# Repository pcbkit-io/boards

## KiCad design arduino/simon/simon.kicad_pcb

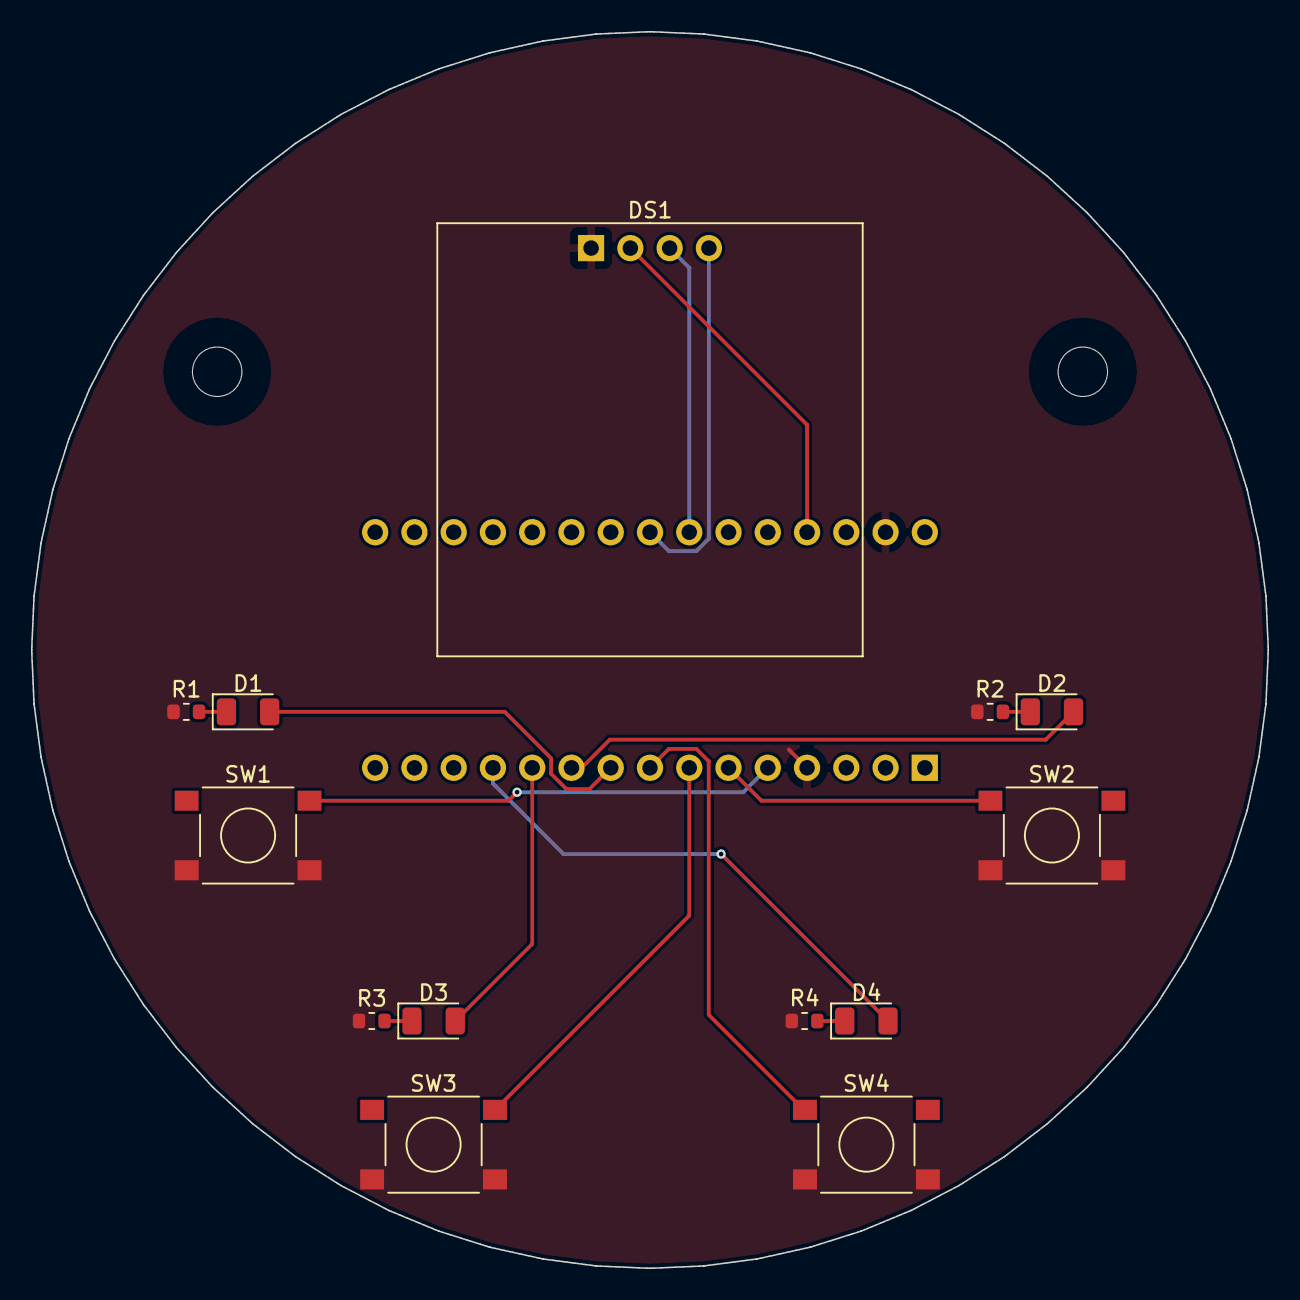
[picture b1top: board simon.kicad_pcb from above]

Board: 2 copper layers, 80.0 x 80.0 mm, 16 parts (1 on the bottom side), 16 nets.

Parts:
D1: green; LED_1206_3216Metric
D2: red; LED_1206_3216Metric
D3: blue; LED_1206_3216Metric
D4: yellow; LED_1206_3216Metric
DS1: SSD1306 0.96in 128x64 I2C OLED module; OLED_0.96in_I2C_Socket_1x04_P2.54mm
H1, H2: MountingHole_3.2mm_M3
NANO: A000005; Arduino_Nano_Socket_2x15_P2.54mm_W15.24mm
R1, R2, R3, R4: 680ohm; R_0603_1608Metric
SW1, SW2, SW3, SW4: PTS645SM43SMTR92 LFS; SW_Tactile_SPST_6x6mm_SMD

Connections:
B1: NANO.5 (D2), SW1.1 (a)
B2: NANO.6 (D3), SW2.1 (a)
B3: NANO.7 (D4), SW3.1 (a)
B4: NANO.8 (D5), SW4.1 (a)
GND: DS1.1 (GND), NANO.4 (GND), NANO.29 (GND), R1.2 (b), R2.2 (b), R3.2 (b), R4.2 (b), SW1.2 (b), SW2.2 (b), SW3.2 (b), SW4.2 (b)
K1: D1.1 (K), R1.1 (a)
K2: D2.1 (K), R2.1 (a)
K3: D3.1 (K), R3.1 (a)
K4: D4.1 (K), R4.1 (a)
L1: D1.2 (A), NANO.9 (D6)
L2: D2.2 (A), NANO.10 (D7)
L3: D3.2 (A), NANO.11 (D8)
L4: D4.2 (A), NANO.12 (D9)
SCL: DS1.3 (SCL), NANO.24 (A5)
SDA: DS1.4 (SDA), NANO.23 (A4)
V5: DS1.2 (VCC), NANO.27 (P5V)

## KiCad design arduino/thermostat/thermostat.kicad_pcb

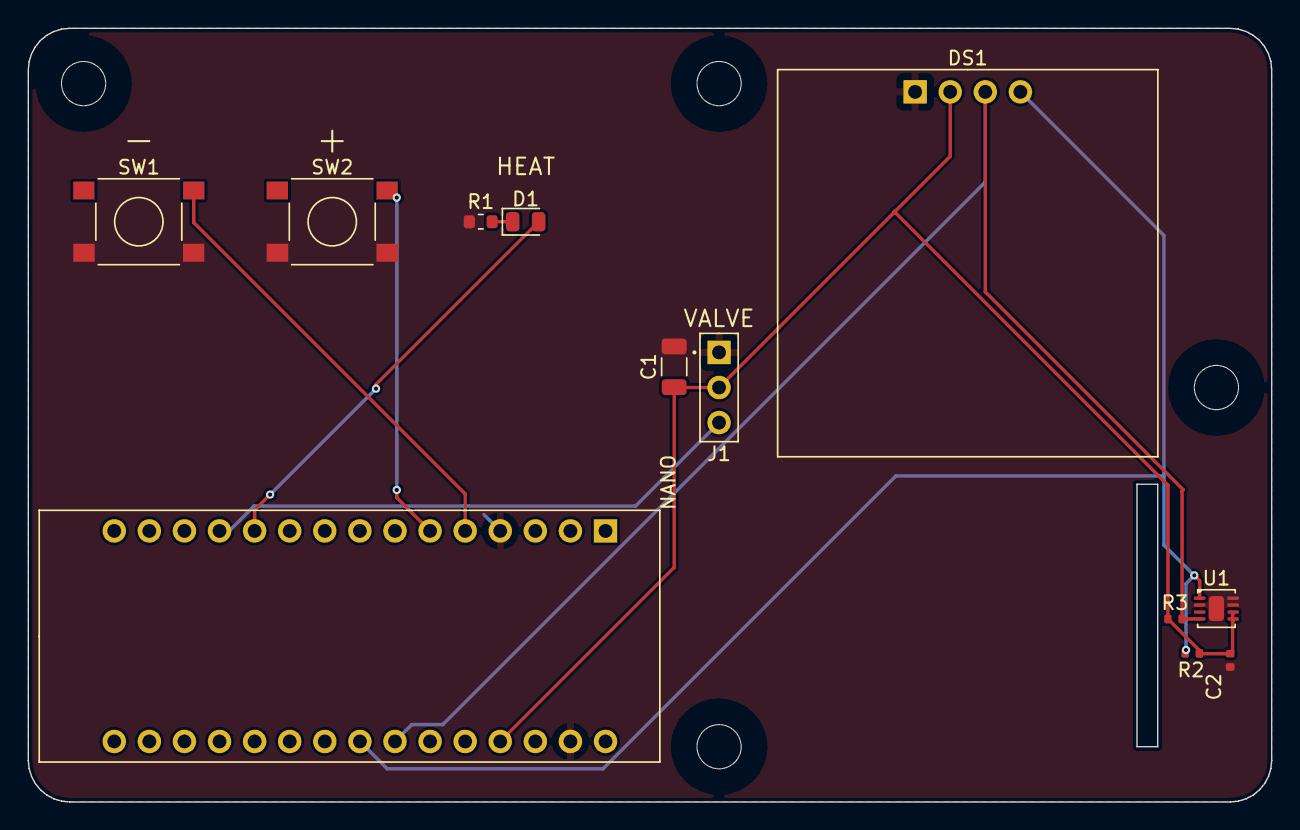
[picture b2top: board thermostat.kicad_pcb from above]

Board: 2 copper layers, 90.0 x 56.0 mm, 16 parts (0 on the bottom side), 9 nets.

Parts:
C1: 100uF; C_1206_3216Metric
C2: 100nF; C_0402_1005Metric
D1: red; LED_0805_2012Metric
DS1: SSD1306 0.96in 128x64 I2C OLED module; OLED_0.96in_I2C_Socket_1x04_P2.54mm
H1, H2, H3, H4: MountingHole_3.2mm_M3
J1: RC servo header, 1 x 3 pins, 2.54 mm; PinHeader_1x03_P2.54mm_Vertical
NANO: A000005; Arduino_Nano_Socket_2x15_P2.54mm_W15.24mm
R1: 1kohm; R_0603_1608Metric
R2, R3: 10kohm; R_0402_1005Metric
SW1, SW2: PTS645SM43SMTR92 LFS; SW_Tactile_SPST_6x6mm_SMD
U1: SHT31-DIS-B2.5kS; DFN-8-1EP_2.5x2.5mm_P0.5mm_EP1.1x1.8mm

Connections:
GND: C1.2 (b), C2.2 (b), DS1.1 (GND), J1.1 (GND), NANO.4 (GND), NANO.29 (GND), R1.2 (b), SW1.2 (b), SW2.2 (b), U1.2 (ADDR), U1.7 (R), U1.8 (VSS), U1.9 (VSS)
HEAT: D1.2 (A), NANO.11 (D8)
HEAT_K: D1.1 (K), R1.1 (a)
MINUS: NANO.5 (D2), SW1.1 (a)
PLUS: NANO.6 (D3), SW2.1 (a)
SCL: DS1.3 (SCL), NANO.24 (A5), R3.2 (b), U1.4 (SCL)
SDA: DS1.4 (SDA), NANO.23 (A4), R2.2 (b), U1.1 (SDA)
V5: C1.1 (a), C2.1 (a), DS1.2 (VCC), J1.2 (VPLUS), NANO.27 (P5V), R2.1 (a), R3.1 (a), U1.5 (VDD), U1.6 (nRESET)
VALVE: J1.3 (SIG), NANO.12 (D9)

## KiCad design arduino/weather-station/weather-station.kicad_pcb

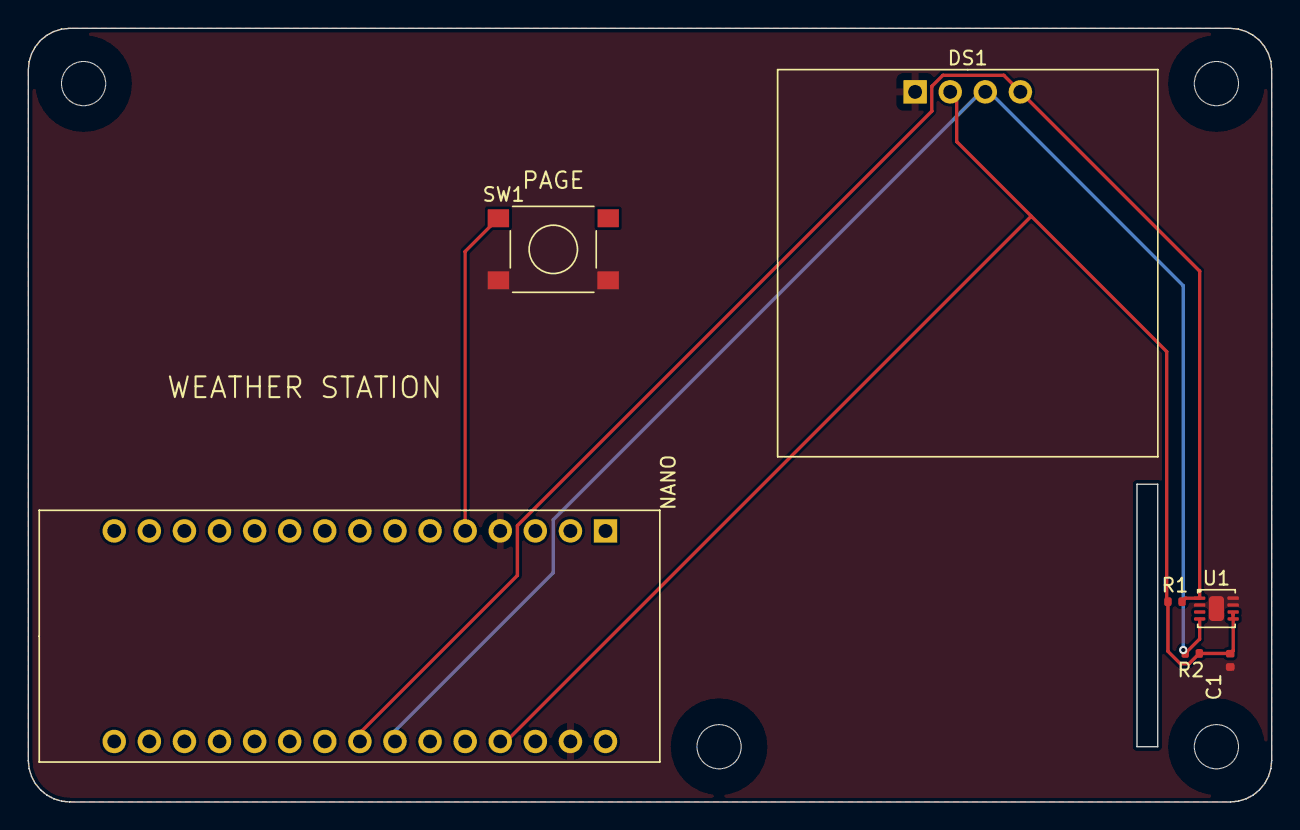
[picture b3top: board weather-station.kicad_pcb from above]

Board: 2 copper layers, 90.0 x 56.0 mm, 11 parts (0 on the bottom side), 5 nets.

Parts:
C1: 100nF; C_0402_1005Metric
DS1: SSD1306 0.96in 128x64 I2C OLED module; OLED_0.96in_I2C_Socket_1x04_P2.54mm
H1, H2, H3, H4: MountingHole_3.2mm_M3
NANO: A000005; Arduino_Nano_Socket_2x15_P2.54mm_W15.24mm
R1, R2: 10kohm; R_0402_1005Metric
SW1: PTS645SM43SMTR92 LFS; SW_Tactile_SPST_6x6mm_SMD
U1: SHT31-DIS-B2.5kS; DFN-8-1EP_2.5x2.5mm_P0.5mm_EP1.1x1.8mm

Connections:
GND: C1.2 (b), DS1.1 (GND), NANO.4 (GND), NANO.29 (GND), SW1.2 (b), U1.2 (ADDR), U1.7 (R), U1.8 (VSS), U1.9 (VSS)
PAGE: NANO.5 (D2), SW1.1 (a)
SCL: DS1.3 (SCL), NANO.24 (A5), R2.2 (b), U1.4 (SCL)
SDA: DS1.4 (SDA), NANO.23 (A4), R1.1 (a), U1.1 (SDA)
V5: C1.1 (a), DS1.2 (VCC), NANO.27 (P5V), R1.2 (b), R2.1 (a), U1.5 (VDD), U1.6 (nRESET)

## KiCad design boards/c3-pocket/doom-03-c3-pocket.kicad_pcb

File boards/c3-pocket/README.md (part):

# 03 · c3-pocket — a Game Boy-shaped RISC-V Doom on an ESP32-C3

A small portrait handheld (52 × 128 mm) around an ESP32-C3-MINI-1 module: one RISC-V core, 400 KB
of SRAM, 4 MB of flash, a 1.3" IPS screen, eight buttons, a piezo and two 18650 cells behind it,
charged from its USB-C port.
The C3 has no PSRAM, so Doom is cut down the way rp2040-doom cut it for the RP2040.

| | |
|---|---|
| Processor | ESP32-C3-MINI-1-H4 (the -N4's 105 °C twin: same pins and 4 MB flash; the -N4 is out of stock at JLCPCB): ESP32-C3, one **RV32IMC** core (Espressif's own, 4-stage pipeline) at 160 MHz, 400 KB SRAM (16 KB of it cache), 384 KB ROM, 4 MB flash in the module (MSPI, XIP through the cache), Wi-Fi/BLE unused |
| Display | 1.3" 240 × 240 IPS, ST7789, SPI without CS (mode 3): GPIO6 SCK, GPIO7 MOSI, GPIO5 D/C, GPIO4 RES; backlight on |
| Input | 8 × 5.1 mm tact switches: d-pad IO0–IO3, fire IO10, use RXD0 (IO20), strafe TXD0 (IO21), menu IO9 (= BOOT: held at reset it enters download mode) |
| Sound | piezo on IO8 (LEDC PWM; IO8 is a strapping pin held high by 10 kΩ, the piezo is DC-open) |
| Power | 2 × 18650 Li-ion in parallel (1S2P) behind reverse-cell (AO3401A) and DW01A + FS8205A protection; BQ24075 charger with power path from USB-C (fuse, TVS); SYS → AP2112K-3.3 LDO, its enable on the slide switch |
| Programming | USB-C to the C3's own USB Serial/JTAG (IO18/IO19): `esptool.py` flashes it, no bridge chip; JTAG debugging over the same cable; RESET on the back, BOOT = MENU |
| Board | 52 × 128 mm, 2 layers, four M3 holes; front: display, buttons, USB-C (left edge, near the top), charger, switch, test pads; back: two 18650 holders, the module (top edge, antenna away from the hand), RESET, piezo |

<!-- STATUS -->
**Board status** (measured on the dev host with PCBKit's CLI): `pcbkit check`: complete — 0 errors, 3 warnings (diff-pair-uncoupled, skew, track-width-class), 0 unrouted nets. 58 components, 40 nets, 502 track segments (1483 mm), 79 vias.
`analysis.run { lens: "ready" }`: Typical scenario, partial. Nothing to fix, 4 to consider, 15 ok: weigh the warnings (tell the person about the ones that are their choice), then the board is ready to order.
`pcbkit export --format fab` succeeds without `--force`: every assembled line of the BOM has an LCSC code.
<!-- /STATUS -->

## Run it in the browser

Open https://app.pcbkit.io/github/pcbkit-io/doom-handheld/tree/main/boards/c3-pocket, open the
Laboratory and press **Build & run**: the page builds `doom/` for the C3's RV32IMC core (with
rp2040-doom's `DOOM1.WHX` linked into the flash), boots it the way the chip's boot ROM boots an
image from flash, and draws the ST7789's frames on the board. Play with the keyboard (arrows,
F fire, Space use, S held to strafe, M menu; fire confirms in the menus) or a gamepad (`input.js`).

## How Doom fits

`doom/` is rp2040-doom's engine (kilograham, GPL-2: its compressed level format and its
`DOOM1.WHX`, the shareware episode in 1.8 MB) on PCBKit's ESP32-C3 kit instead of ESP-IDF: the
WHX and the constant tables read in place from the flash through the cache, the zone heap in the
DRAM (190 KB of data and bss, 70 KB of heap inside the 256 KiB its 16-bit pointers reach), the CPU
at 160 MHz. Each 320 × 200 frame is scaled by 3/4 into the panel's middle 240 × 150 (of four
columns or lines the middle two averaged), RGB565 over GP-SPI2 at 40 MHz in SPI mode 3 (the
module has no chip select): 72 KB per frame, 14 ms. The eight buttons are read from their GPIOs
(pulled up). The firmware is silent: the piezo is not driven yet.

## Power

| State | Current (estimate) |
|---|---|
| ESP32-C3 at 160 MHz, radio off | 25–30 mA |
| ST7789 1.3" with backlight | 20–30 mA |
| **Total** | **~55 mA at 3.3 V** |

Two 18650 Li-ion cells in Keystone 1042 holders on the back, upright side by side, in parallel
(1S2P, 3.0–4.2 V). From the cells to the module:

- **Reverse cells:** an AO3401A P-MOSFET in the plus line, its gate at the cells' minus: cells put
  in backwards leave it off and the board unpowered (it conducts both ways when they are right, so
  charging goes through it too). It cannot help one cell reversed against the other: in parallel
  they would short each other, so check both against the silkscreen's + (at the top end of each
  holder) before closing a case.
- **Protection:** DW01A + FS8205A in the pack's minus: over-charge 4.3 V, over-discharge 2.4 V,
  over-current about 3 A and short circuit, for the pack. Flat-top unprotected 18650 cells fit
  the holders.
- **USB-C input:** 5.1 kΩ on CC1 and CC2 (any USB-C charger or computer gives 5 V), a 750 mA
  resettable fuse (nSMD075), a 5 V TVS (SMF5.0A), and a USBLC6-2 ESD array on D+/D−.
- **Charger with power path:** a TI BQ24075 in USB500 mode (at most 500 mA from the port), ISET
  for 800 mA (RISET 1.13 kΩ), RILIM 1.18 kΩ, safety timers off (two cells in parallel charge longer
  than its longest timer; termination is by current), TS tied to 10 kΩ (no thermistor). A linear
  charger passes on at most what it takes in, so from USB the cells charge at up to about 500 mA.
  Its output SYS runs the board from USB when one is plugged in and from the cells otherwise.
- **3.3 V:** the AP2112K-3.3 LDO from SYS (about 25 mV dropout at this board's 55 mA): 3.3 V down
  to about 3.33 V on the cells, then it follows them; the C3 runs to 3.0 V, so the game runs until
  the cells are nearly empty.
- **On/off:** the slide switch on the right edge drives the LDO's enable (1 MΩ pulls it off); the
  charger charges with the switch off; off, the board draws only the charger's and the
  protection's few µA.

Two 3000 mAh cells (about 22 Wh) at ~0.2 W: **about 100 h** of play (estimate). A full charge of
two empty cells from USB at about 500 mA takes about 12 h.

## Charging

Plug any USB-C charger or computer into J1 (the left edge, near the top). The red LED (CHG) is on
while the cells charge and goes out when they are full; the green LED (USB) is on while USB power
is present. The board runs from USB while it charges, switched on or off. Insert the cells with +
at the end the back's silkscreen marks (the top).

## Modules plugged in by hand

The assembly solders a 1x7 female socket for the display; the module is bought separately:

- **DS1: 1.3" 240 × 240 ST7789 IPS module, SPI without CS** (7 pins: GND, VCC, SCL, SDA, RES, DC,
  BLK), its pin header soldered on as it comes, plugged in on the front.

## Check warnings and why they stay

| Warning | Why it is acceptable |
|---|---|
| `diff-pair-uncoupled` and `skew` on DP / DN (a few tens of mm uncoupled, a few mm of skew) | USB 2.0 full speed (12 Mbit/s, 83 ns a bit): the connector is on the front, the C3 on the back; tens of mm uncoupled and 6 mm of skew (about 40 ps) are nothing at this rate |
| `track-width-class` on GND: about 1 mm narrowed to 0.19 mm, at a via beside the LDO and the module's decoupling | a local ground stub between parts packed under the module; it lies inside the ground pours of both sides, which carry the ground current |

## Firmware: build and flash

- **Build:** in PCBKit, the Laboratory's **Build & run** builds `doom/` (RV32IMC, the kit's
  start-up and link layout); then export the firmware (`export.run { format: "firmware" }`):
  `U1.bin`, the whole flash from offset 0 (the boot image the ROM loads, then the program's code
  and constants and the WHX at their pages). No 2nd-stage bootloader or partition table: the ROM
  boots the image directly.
- **Flashing on arrival:** switch the board on and plug its USB-C into a computer: the C3's USB
  Serial/JTAG enumerates (303a:1001, `/dev/ttyACM0` or a COM port) even with the module's flash
  blank, and `esptool` resets the chip into its ROM download mode through it by itself:
  `esptool.py --chip esp32c3 -p /dev/ttyACM0 write_flash 0x0 U1.bin` (or the browser's ESP Web
  Flasher at offset 0). If a running program has taken the USB pins over: hold MENU (IO9, the
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
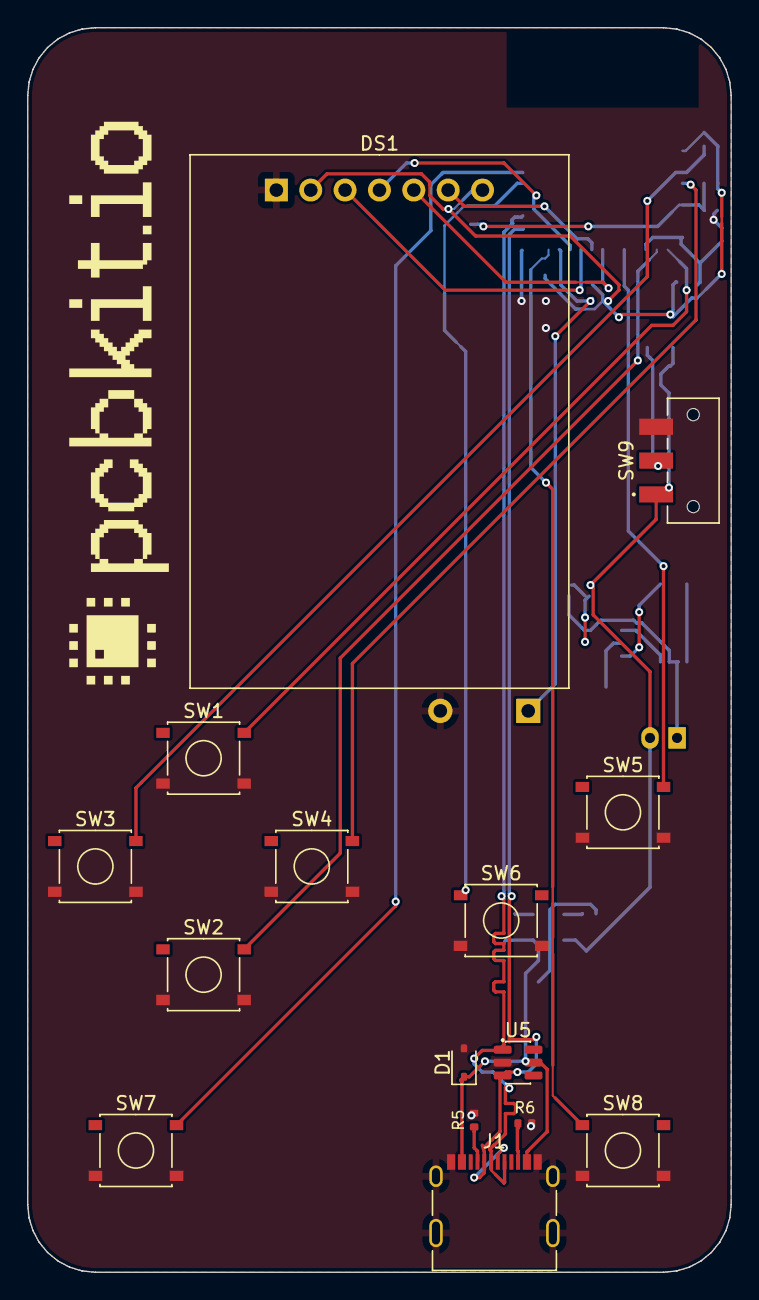
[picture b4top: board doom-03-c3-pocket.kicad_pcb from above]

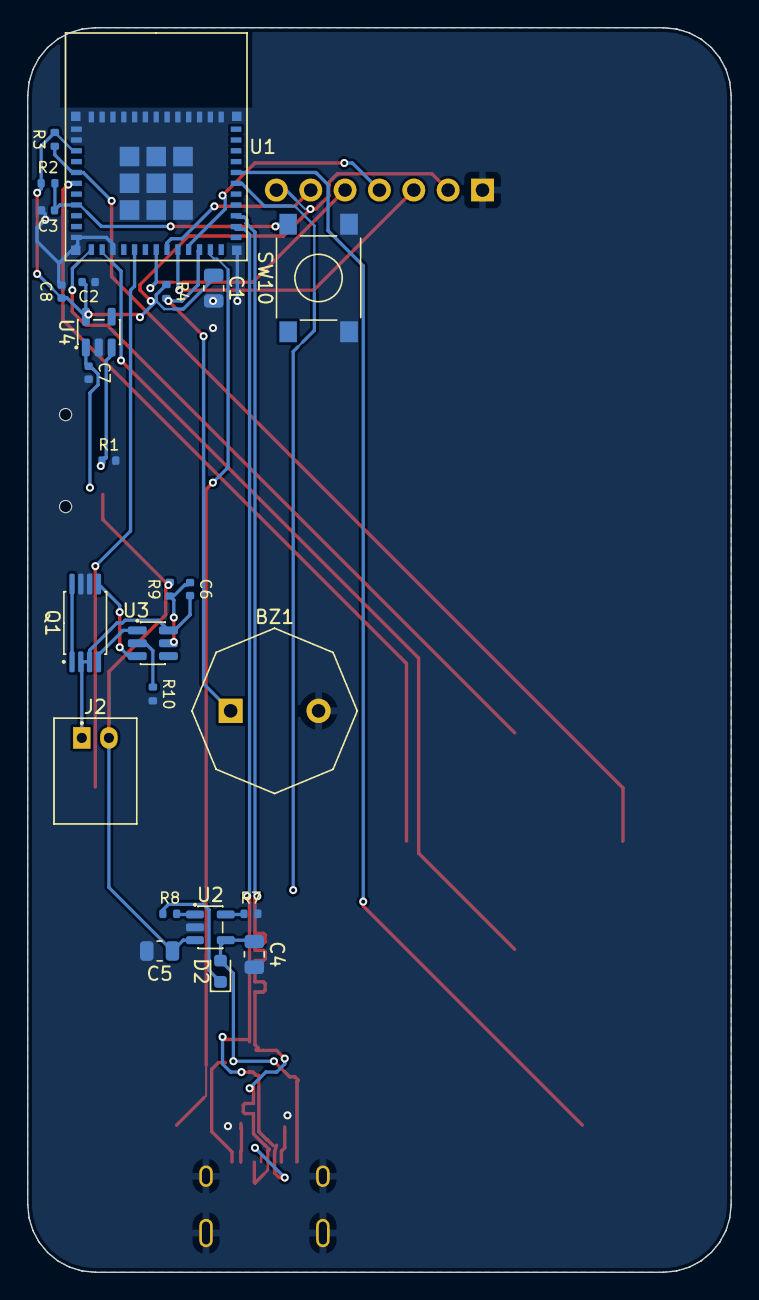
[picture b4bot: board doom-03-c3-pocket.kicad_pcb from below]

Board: 2 copper layers, 52.0 x 92.0 mm, 41 parts (25 on the bottom side), 32 nets.

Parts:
BZ1: GPC12075YB-5V4000; Buzzer_D12.0mm_H7.5mm_P6.50mm
C1: 10uF; C_0805_2012Metric
C2, C6: 100nF; C_0402_1005Metric
C3, C7, C8: 1uF; C_0402_1005Metric
C4, C5: 4.7uF; C_0805_2012Metric
D1: tvs 5V; D_SOD-323
D2: red; LED_0603_1608Metric
DS1: MSP1308 1.3in 240x240 IPS SPI module (ST7789); TFT_1.3in_ST7789_Socket_1x07_P2.54mm
J1: USB_C_Receptacle_USB2.0_16P
J2: S2B-PH-K-S(LF)(SN); JST_PH_S2B-PH-K_1x02_P2.00mm_Horizontal
Q1: FS8205A; TSSOP-8_4.4x2.93mm_P0.65mm
R1: 100kohm; R_0402_1005Metric
R2, R3, R4: 10kohm; R_0402_1005Metric
R5, R6: 5.1kohm; R_0402_1005Metric
R7: 2kohm; R_0402_1005Metric
R8: 470ohm; R_0402_1005Metric
R9: 100ohm; R_0402_1005Metric
R10: 1kohm; R_0402_1005Metric
SW1, SW2, SW3, SW4, SW5, SW6, SW7, SW8: TS-1187A-B-A-B; SW_Tactile_SPST_5.1x5.1mm_SMD
SW9: JS102011SAQN; SW_Slide_SPDT_CK_JS102011SAQN_Horizontal
SW10: PTS645SM43SMTR92 LFS; SW_Tactile_SPST_6x6mm_SMD
U1: ESP32-C3-MINI-1-N4X; ESP32-C3-MINI-1_module_13.2x16.6mm_LGA_53_pads
U2: MCP73831T-2ACI/OT; SOT-23-5
U3: DW01A; SOT-6_1.6x2.9mm_P0.95mm
U4: AP2112K-3.3TRG1; SOT-23-5
U5: ESD 2-line; SOT-23-6
logo: Logo_PCBKit_pcbkit.io

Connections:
BAT_N: C6.2, J2.1, Q1.2, Q1.3, U3.6
BUZZ: BZ1.1, R4.2, U1.22
DN: J1.A7, J1.B7, U1.26, U5.3
DOWN: SW2.1, SW2.2, U1.13
DP: J1.A6, J1.B6, U1.27, U5.1
EN: C3.1, R2.2, SW10.1, SW10.2, U1.8
FIRE: SW5.1, SW5.2, U1.16
GND: BZ1.2, C1.2, C2.2, C3.2, C4.2, C5.2, C7.2, C8.2, D1.2, DS1.1, J1.A1, J1.B1, J1.S1, Q1.6, Q1.7, R1.2, R5.2, R6.2, R7.2, R10.2, SW1.3, SW1.4, SW2.3, SW2.4, SW3.3, SW3.4, SW4.3, SW4.4, SW5.3, SW5.4, SW6.3, SW6.4, SW7.3, SW7.4, SW8.3, SW8.4, SW9.3, SW10.3, SW10.4, U1.1, U1.2, U1.11, U1.14, U1.36, U1.37, U1.38, U1.39, U1.40, U1.41, U1.42, U1.43, U1.44, U1.45, U1.46, U1.47, U1.48, U1.49, U1.50, U1.51, U1.52, U1.53, U2.2, U4.2, U5.2
LCD_DC: DS1.6, U1.19
LCD_RST: DS1.5, U1.18
LDO_EN: R1.1, SW9.2, U4.3
LEFT: R3.1, SW3.1, SW3.2, U1.5
MENU: SW8.1, SW8.2, U1.23
MOSI: DS1.4, U1.21
unnamed: C6.1, R9.1, U3.5
unnamed: Q1.4, U3.1
unnamed: Q1.5, U3.3
unnamed: R7.1, U2.5
unnamed: R8.2, U2.1
unnamed: R10.1, U3.2
RIGHT: SW4.1, SW4.2, U1.6
SCK: DS1.3, U1.20
STRAFE: SW7.1, SW7.2, U1.31
U2Support/LED_K: D2.1, R8.1
U3Support/DRAIN: Q1.1, Q1.8
UP: SW1.1, SW1.2, U1.12
USE: SW6.1, SW6.2, U1.30
V3: C1.1, C2.1, C8.1, DS1.2, DS1.7, R2.1, R3.2, R4.1, U1.3, U4.5
VBAT: C5.1, C7.1, J2.2, R9.2, SW9.1, U2.3, U4.1
VBUS: C4.1, D1.1, D2.2, J1.A4, J1.B4, U2.4, U5.5
usb/power/cc1: J1.A5, R5.1
usb/power/cc2: J1.B5, R6.1

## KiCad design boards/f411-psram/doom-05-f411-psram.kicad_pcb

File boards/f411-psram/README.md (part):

# 05 · f411-psram — an STM32 "Black Pill" chip with 8 MB of SPI PSRAM

The STM32F411CEU6 (the chip of WeAct's Black Pill) is a fast Cortex-M4F with only 128 KB of SRAM and
no memory-mapped QSPI, so the board adds an 8 MB APS6404L PSRAM and a 16 MB W25Q128 on SPI1 and the
port pages Doom's heap through a software cache. A 2.0" IPS, an I2S amplifier, eight buttons, and two
18650 cells it charges from its USB-C. Firmware goes in through the same USB-C by the ROM's USB DFU
bootloader, or SWD. JLCPCB assembles everything but the display module, which plugs into the socket
it solders.

| | |
|---|---|
| Processor | STM32F411CEU6 (UFQFPN-48): Arm **Cortex-M4F** (ARMv7E-M, Thumb-2, DSP, single-precision FPU), 100 MHz, 128 KB SRAM, 512 KB flash with ART accelerator; 25 MHz HSE crystal |
| Memory | APS6404L-3SQR 8 MB PSRAM (CS PA4) and W25Q128JV 16 MB flash (CS PB2) on SPI1 at 50 MHz (PA5 SCK, PA6 MISO, PA7 MOSI) |
| Display | 2.0" 240 × 320 IPS, ST7789 (MSP2008), SPI2 at 25 MHz (PB13 SCK, PB15 MOSI, PB12 CS, PB14 DC, PB1 RES), backlight PWM on PB10 (TIM2_CH3); used landscape 320 × 240 |
| Input | 8 × 6 mm tact switches: up PA1, down PA2, left PA3, right PB4, fire PB6, use PB7, strafe PB8, menu PB0 (internal pull-ups) |
| Sound | I2S3 (PB3 CK, PA15 WS, PB5 SD) → MAX98357A (mono mix, 9 dB) → 8 Ω speaker |
| Power | 2 × 18650 Li-ion in parallel (1S2P) in Keystone 1042 holders → reverse-cell P-FET (AO3401A) → DW01A + FS8205A; BQ24075 charger with power path from USB-C; SYS → TLV75533 LDO (3.3 V, switched by its EN) and the amplifier |
| Programming | USB-C to PA11/PA12: hold BOOT (BOOT0 → 3.3 V) and press RESET → ROM DFU (`dfu-util`); SWD header J1 on the back (VCC, SWDIO, SWCLK, NRST, GND) for an ST-LINK |
| Board | 140 × 104 mm, **4 layers**, four M3 holes; front: display, buttons, BOOT, RESET, on/off switch, USB-C (top edge), charger, speaker connector (right edge), test pads; back: MCU, memories, amplifier, regulator, SWD header, the two cells |

<!-- STATUS -->
**Board status** (measured on the dev host with PCBKit's CLI): `pcbkit check`: complete — 0 errors, 2 warnings (diff-pair-uncoupled, skew), 0 unrouted nets; `issues` has 2 of 2. 79 components, 60 nets, 866 track segments (2431 mm), 93 vias.
`analysis.run { lens: "ready" }`: Typical scenario, partly by family estimates. Nothing to fix, 4 to consider, 14 ok: weigh the warnings (tell the person about the ones that are their choice), then the board is ready to order.
`pcbkit export --format fab` succeeds without `--force`: every assembled line of the BOM has an LCSC code.
<!-- /STATUS -->

Warnings left, and why they are acceptable:

| Warning | Why |
|---|---|
| `diff-pair-uncoupled`, `skew` on DP / DN | USB full speed (12 Mbit/s, used only by the ROM's DFU): the connector is on the front's top edge, the processor on the back; tens of mm uncoupled and a few mm of skew are harmless at this rate |
| J1 is not on an edge | the SWD header, for a programmer's clip during development: not a cable that stays |
| heat sources need exact thermal parameters; chips estimated by their family | the thermal estimate's own caveat: nothing on this board dissipates more than a few hundred mW |

## Run it in the browser

Open https://app.pcbkit.io/github/pcbkit-io/doom-handheld/tree/main/boards/f411-psram, open the
Laboratory and press **Build & run**: the page builds both programs — `emu/` for the STM32F411
(Cortex-M4F) and `doom/` for the computer it emulates (pcbkit-virt, with `DOOM1.WAD` linked in) —
puts the second in the W25Q128 and runs the board.

## How Doom fits

The F411 has 128 KB of SRAM and no memory-mapped QSPI, so its firmware (`emu/`, 19.5 KB) is a
RISC-V computer built from the serial chips, as on doom-01: an RV32IMAC interpreter
(`emu/rvemu.c`) with a 64 KB direct-mapped write-back cache (2048 lines of 32 bytes) in its SRAM
over the APS6404L (the guest's 8 MB of RAM) and the W25Q128 (the guest, `doom/`: Doom for
pcbkit-virt with the WAD linked in, its code and constants read where they lie). A miss is one
SPI transaction at 50 MHz with fast read (0Bh): 5.9 µs with the chip selected, inside the
PSRAM's 8 µs limit. Each guest frame (320 × 200, 8-bit) goes to the ST7789 through the guest's
colour table as RGB565, on SPI2 at 25 MHz. Measured in PCBKit's simulator: the title screen at
about 40 s of device time, in full colour; then the demo, a few frames a second.

## Power

Two 18650 Li-ion cells in Keystone 1042 holders on the back, in parallel (1S2P, 3.0–4.2 V). From the
cells to the board:

- **Reverse cells:** an AO3401A P-MOSFET in the plus line, its gate at the cells' minus: cells put
  in backwards leave it off and the board unpowered (it conducts both ways when they are right, so
  charging goes through it too). It cannot help one cell reversed against the other: in parallel
  they would short each other, so check both against the silkscreen's + before closing a case.
- **Protection:** DW01A + FS8205A in the pack's minus: over-charge 4.3 V, over-discharge 2.4 V,
  over-current about 3 A and short circuit, for the pack.
- **Charger with power path:** a TI BQ24075 from the USB-C's VBUS (5.1 kΩ CC pull-downs: any USB-C
  charger gives 5 V), in USB500 mode (at most 500 mA from the port), 800 mA fast charge (RISET
  1.13 kΩ), input limit by RILIM 1.18 kΩ, safety timers off (two cells charge longer than its
  longest timer; termination is by current), TS tied to 10 kΩ (no thermistor). Its output SYS runs
  the board from USB when one is plugged in and from the cells otherwise.
- **Rails:** SYS feeds the TLV75533 LDO (3.3 V for the MCU, memories and display) and the
  MAX98357A directly. Near empty (3.0–3.3 V cells) the LDO drops out and 3.3 V follows the cells
  down; the F411, the memories and the ST7789 run to 2.7 V.
- **On/off:** the slide switch on the left edge drives the LDO's enable (off: the 3.3 V rail is off
  and the amplifier is shut down by its SD_MODE pull-up; the charger still charges).

| State | Current (estimate) |
|---|---|
| STM32F411 at 100 MHz | ~25 mA |
| PSRAM + flash active | ~15 mA |
| ST7789 2.0" with backlight | ~40 mA |
| MAX98357A playing | 20–200 mA from SYS |
| **Typical** | **~110 mA at 3.7 V** |

Two 3000 mAh cells → **~50 h**. A full charge of two empty cells at 800 mA takes about 8 h.

## Charging

Plug any USB-C charger or computer into the USB-C on the top edge. The red LED (CHG) is on while the
cells charge and goes out when they are full; the green LED (USB) is on while USB power is present.
The board runs from USB while it charges, switched on or off. Insert the cells with + at the end the
back's silkscreen marks.

## Modules plugged in by hand

The assembly solders a 1x8 female socket; the module is bought separately and plugged in:

- **DS1: 2.0" 240 × 320 ST7789 IPS SPI module** (MSP2008-type, 8 pins: GND, VCC, SCL, SDA, RES, DC,
  CS, BLK), on the front.
- An 8 Ω speaker (1–3 W) on the JST PH 2-pin connector J5 at the right edge.

## Firmware: build and flash

- **Build:** in PCBKit, the Laboratory's **Build & run** builds both programs (the F411's for
  Cortex-M4F with hard float; the guest for RV32IMAC with the WAD); then export the firmware
  (`export.run { format: "firmware" }`): `U1.bin` for the STM32F411 and `U3.bin` for the W25Q128.
- **The STM32F411, on arrival:** switch the board on, plug its USB-C into a computer, hold BOOT and
  press and release RESET (then release BOOT): the F411's ROM boot loader enumerates as "STM32
  BOOTLOADER" (USB DFU, 0483:df11). Then `dfu-util -a 0 -s 0x08000000:leave -D U1.bin` (or
  STM32CubeProgrammer). The ROM's DFU needs the 25 MHz HSE, which is fitted. Or over SWD: an
  ST-LINK on J1 (VCC, SWDIO, SWCLK, NRST, GND), `st-flash write U1.bin 0x8000000`.
- **The W25Q128 (the guest):** hold MENU while switching on: the firmware lets go of the memory bus
  and waits, so a USB SPI programmer (CH341A) with a SOIC-8 clip on the W25Q128 writes it in
  place: `flashrom -p ch341a_spi -w U3.bin`. Switch off and on: Doom boots.

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
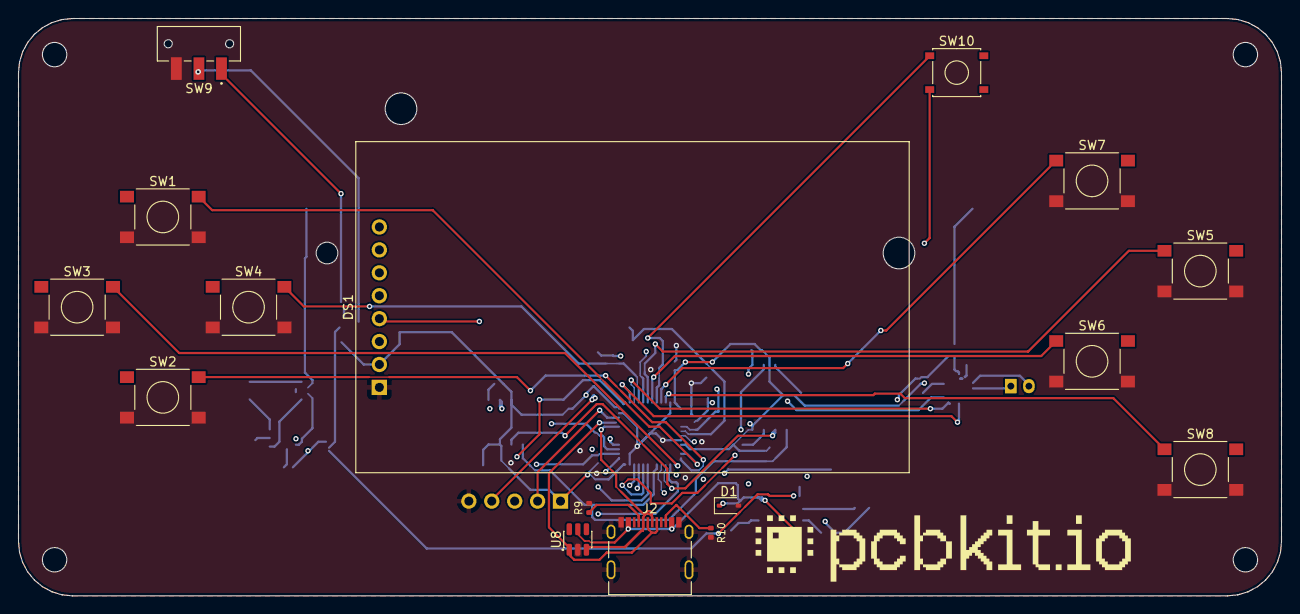
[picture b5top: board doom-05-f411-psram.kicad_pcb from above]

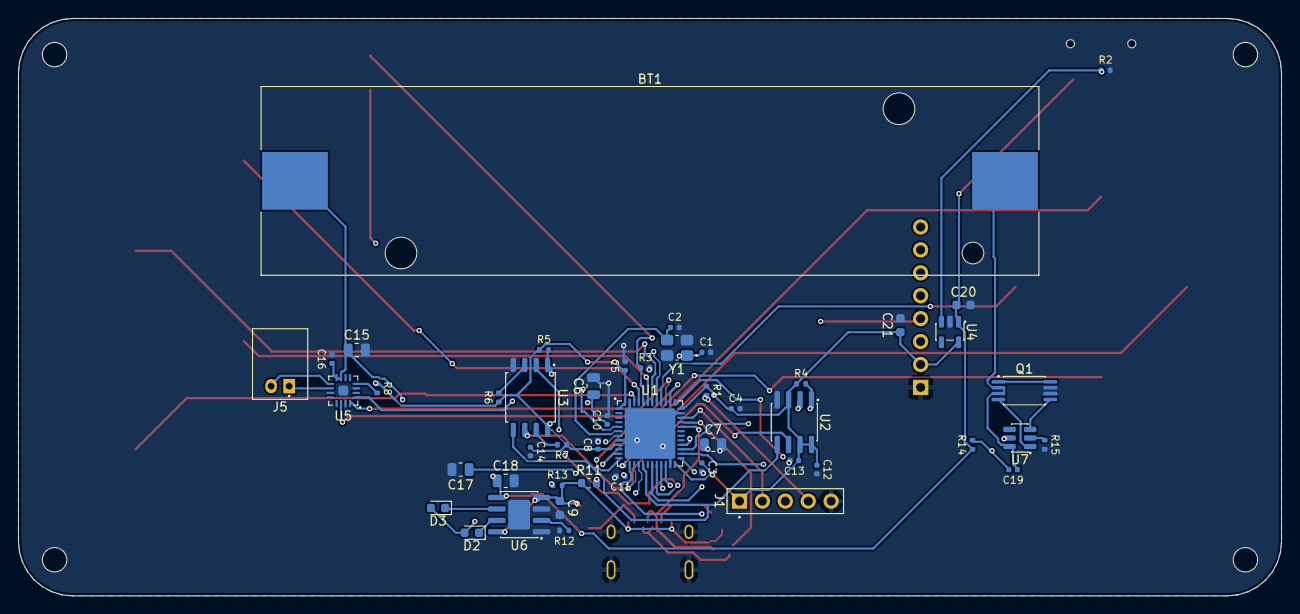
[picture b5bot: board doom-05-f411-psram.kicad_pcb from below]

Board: 4 copper layers, 140.0 x 64.0 mm, 69 parts (48 on the bottom side), 54 nets.

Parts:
BT1: 1042; BatteryHolder_Keystone_1042_1x18650
C1, C2: 15pF; C_0402_1005Metric
C3, C4, C5, C8, C11, C13, C14, C16, C19: 100nF; C_0402_1005Metric
C6, C7: 4.7uF; C_0805_2012Metric
C9, C20, C21: 1uF; C_0603_1608Metric
C10, C12: 1uF; C_0402_1005Metric
C15, C17, C18: 10uF; C_0805_2012Metric
D1: tvs 5V; D_SOD-323
D2: red; LED_0603_1608Metric
D3: green; LED_0603_1608Metric
DS1: MSP2008 2.0in 240x320 IPS SPI module (ST7789); TFT_2.0in_ST7789_Socket_1x08_P2.54mm
H1, H2, H3, H4: MountingHole_2.7mm_M2.5
J1: PinHeader_1x05_P2.54mm_Vertical
J2: USB_C_Receptacle_USB2.0_16P
J5: S2B-PH-K-S(LF)(SN); JST_PH_S2B-PH-K_1x02_P2.00mm_Horizontal
Q1: FS8205A; TSSOP-8_4.4x2.93mm_P0.65mm
R1, R3, R4, R5, R6, R7: 10kohm; R_0402_1005Metric
R2: 100kohm; R_0402_1005Metric
R8: 634kohm; R_0402_1005Metric
R9, R10: 5.1kohm; R_0402_1005Metric
R11: 1ohm; R_0603_1608Metric
R12: 1.2kohm; R_0402_1005Metric
R13, R15: 1kohm; R_0402_1005Metric
R14: 100ohm; R_0402_1005Metric
SW1, SW2, SW3, SW4, SW5, SW6, SW7, SW8: PTS645SM43SMTR92 LFS; SW_Tactile_SPST_6x6mm_SMD
SW9: JS102011SAQN; SW_Slide_SPDT_CK_JS102011SAQN_Horizontal
SW10: TS-1187A-B-A-B; SW_Tactile_SPST_5.1x5.1mm_SMD
U1: STM32F411CEU6; QFN-48-1EP_7x7mm_P0.5mm_EP5.6x5.6mm
U2: APS6404L-3SQR-SN; SOIC-8_3.9x4.9mm_P1.27mm
U3: W25Q128JVSIQ; SOIC-8_5.23x5.28mm_P1.27mm
U4: TLV75533PDBVR; SOT-23-5
U5: MAX98357AETE+T; QFN-16-1EP_3x3mm_P0.5mm_EP1.1x1.1mm
U6: TP4056; SOIC-8-1EP_3.9x4.9mm_P1.27mm_EP2.413x3.302mm
U7: DW01A; SOT-6_1.6x2.9mm_P0.95mm
U8: ESD 2-line; SOT-23-6
Y1: 25MHz 10pF; Crystal_SMD_3225-4Pin
logo: Logo_PCBKit_pcbkit.io

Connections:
BAT_N: BT1.2, C19.1, Q1.2, Q1.3, U7.6
BOOT0: R3.1, SW10.1, SW10.2, U1.44
DN: J2.A7, J2.B7, U1.32, U8.3
DOWN: SW2.1, SW2.2, U1.12
DP: J2.A6, J2.B6, U1.33, U8.1
FIRE: SW5.1, SW5.2, U1.42
GND: C1.2, C2.2, C3.2, C4.2, C5.2, C6.2, C7.2, C8.2, C9.2, C10.2, C11.2, C12.2, C13.2, C14.2, C15.2, C16.2, C17.2, C18.2, C20.2, C21.2, D1.2, DS1.1, J1.5, J2.A1, J2.B1, J2.S1, Q1.6, Q1.7, R2.2, R3.2, R9.2, R10.2, R12.2, R15.2, SW1.3, SW1.4, SW2.3, SW2.4, SW3.3, SW3.4, SW4.3, SW4.4, SW5.3, SW5.4, SW6.3, SW6.4, SW7.3, SW7.4, SW8.3, SW8.4, SW9.3, U1.8, U1.23, U1.35, U1.47, U1.49, U2.4, U3.4, U4.2, U5.3, U5.11, U5.15, U5.17, U6.1, U6.3, U6.9, U8.2, Y1.2, Y1.4
I2S_CK: U1.39, U5.16
I2S_SD: U1.41, U5.1
I2S_WS: U1.38, U5.14
LCD_BL: DS1.8, U1.21
LCD_CS: DS1.7, U1.25
LCD_DC: DS1.6, U1.27
LCD_MOSI: DS1.4, U1.28
LCD_RST: DS1.5, U1.19
LCD_SCK: DS1.3, U1.26
LDO_EN: R2.1, SW9.2, U4.3
LEFT: SW3.1, SW3.2, U1.13
MEM_MISO: U1.16, U2.2, U3.2
MEM_MOSI: U1.17, U2.5, U3.5
MEM_SCK: U1.15, U2.6, U3.6
MENU: SW8.1, SW8.2, U1.46
NRST: C11.1, J1.4, R1.2, U1.7
unnamed: C1.1, U1.5, Y1.1
unnamed: C2.1, U1.6, Y1.3
unnamed: C7.1, U1.22
unnamed: C19.2, R14.2, U7.5
unnamed: D2.1, U6.7
unnamed: D3.1, U6.6
unnamed: Q1.4, U7.1
unnamed: Q1.5, U7.3
unnamed: R6.2, U3.3
unnamed: R7.2, U3.7
unnamed: R8.2, U5.4
unnamed: R12.1, U6.2
unnamed: R15.1, U7.2
RAM_CS: R4.2, U1.14, U2.1
RIGHT: SW4.1, SW4.2, U1.40
ROM_CS: R5.2, U1.20, U3.1
SPK_N: J5.1, U5.10
SPK_P: J5.2, U5.9
STRAFE: SW7.1, SW7.2, U1.45
SWCLK: J1.3, U1.37
SWDIO: J1.2, U1.34
U6Support/C1_P: C17.1, R11.2
U6Support/LED_A: D2.2, D3.2, R13.1
U7Support/DRAIN: Q1.1, Q1.8
UP: SW1.1, SW1.2, U1.11
USE: SW6.1, SW6.2, U1.43
V3: C3.1, C4.1, C5.1, C6.1, C8.1, C10.1, C12.1, C13.1, C14.1, C21.1, DS1.2, J1.1, R1.1, R4.1, R5.1, R6.1, R7.1, R8.1, SW10.3, SW10.4, U1.1, U1.9, U1.24, U1.36, U1.48, U2.3, U2.7, U2.8, U3.8, U4.5
VBAT: BT1.1, C15.1, C16.1, C18.1, C20.1, R14.1, SW9.1, U4.1, U5.7, U5.8, U6.5
VBUS: C9.1, D1.1, J2.A4, J2.B4, R11.1, R13.2, U6.4, U6.8, U8.5
usb/power/cc1: J2.A5, R9.1
usb/power/cc2: J2.B5, R10.1

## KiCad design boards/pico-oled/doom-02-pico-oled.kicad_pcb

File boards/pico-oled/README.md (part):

# 02 · pico-oled — a through-hole Doom kit on a Raspberry Pi Pico

A Raspberry Pi Pico (RP2040) on sockets behind a 2.42" monochrome OLED, eight buttons, a piezo and
two 18650 Li-ion cells it charges from the Pico's micro-USB. JLCPCB assembles everything but the two
modules, which plug into the sockets it solders. The game is kilograham's **rp2040-doom** (the full shareware game in the
Pico's 2 MB flash, 264 KB of RAM) with its VGA/DVI back end replaced by a 1-bit OLED back end.

| | |
|---|---|
| Processor | Raspberry Pi Pico (SC0915): RP2040, 2 × Arm **Cortex-M0+** (ARMv6-M, Thumb), up to 133 MHz (rp2040-doom runs it at 270 MHz overclocked), 264 KB SRAM, 2 MB QSPI flash on the module |
| Display | 2.42" 128 × 64 OLED module, SSD1309, 4-wire SPI on SPI0 (GP18 SCK, GP19 MOSI, GP17 CS, GP20 D/C, GP21 RES) |
| Input | 8 × 6 mm tact switches to GND: d-pad GP2–GP5, fire GP6, use GP7, strafe GP8, menu GP9 (internal pull-ups) |
| Sound | passive piezo GPC12075YB on GP15 (PWM) through 100 Ω |
| Power | 2 × 18650 Li-ion in parallel (1S2P, 3.0–4.2 V) behind reverse-cell (AO3401A) and DW01A + FS8205A protection; BQ24075 charger with power path from the Pico's USB; SYS → 1N5819HW → Pico VSYS; the Pico's RT6150 buck-boost makes 3.3 V |
| Programming | the Pico's micro-USB: hold BOOTSEL, plug in, copy `doom.uf2` to the RPI-RP2 drive (the same port charges) |
| Board | 150 × 100 mm, 2 layers, four M3 holes; front: OLED, buttons, charger, on/off switch, test pads; back: Pico (USB end at the top edge), two 18650 holders, piezo |

<!-- STATUS -->
**Board status** (measured on the dev host with PCBKit's CLI): `pcbkit check`: complete — 0 errors, 0 warnings, 0 unrouted nets. 43 components, 37 nets, 339 track segments (1685 mm), 24 vias.
`analysis.run { lens: "ready" }`: Typical scenario, partial. Nothing to fix, 1 to consider, 12 ok: weigh the warnings (tell the person about the ones that are their choice), then the board is ready to order.
`pcbkit export --format fab` succeeds without `--force`: every assembled line of the BOM has an LCSC code.
<!-- /STATUS -->

## Run it in the browser

Open https://app.pcbkit.io/github/pcbkit-io/doom-handheld/tree/main/boards/pico-oled, open the
Laboratory and press **Build & run**: the page builds `doom/` for the Pico's Cortex-M0+ (with
rp2040-doom's `DOOM1.WHX` linked into the 2 MB flash), boots it the way the RP2040's boot ROM does
and draws the OLED's frames on the board. Play with the keyboard (arrows, F fire, Space use, S held
to strafe, M menu; fire confirms in the menus) or a gamepad (`input.js`).

## Why it runs Doom

rp2040-doom (Graham Sanderson, 2021, GPL-2) did the hard part: Doom's WAD compressed into its "WHD"
format (the shareware episode in 1.8 MB), static tables in flash, the zone heap cut to fit 264 KB.
`doom/` is its engine on PCBKit's RP2040 kit instead of the Pico SDK: one core at 200 MHz (the core
voltage raised to 1.15 V first, as the SDK does above 133 MHz), the WHX read in place from the
flash. Each composed 320 × 200 frame is reduced to 128 × 64 (each pixel the mean brightness of
what it covers), its levels stretched from the previous frame's histogram (Doom is dim and of few
tones), dithered to one bit by Atkinson's diffusion and sent as 1 KB over SPI at 10 MHz (0.8 ms).

## Power

Two 18650 Li-ion cells in Keystone 1042 holders on the back, in parallel (1S2P, 3.0–4.2 V, about
5–7 Ah together). From the cells to the Pico:

- **Reverse cells:** an AO3401A P-MOSFET in the plus line, its gate at the cells' minus: cells put
  in backwards leave it off and the board unpowered (it conducts both ways when they are right, so
  charging goes through it too). It cannot help one cell reversed against the other: in parallel
  they would short each other, so check both against the silkscreen's + before closing a case.
- **Protection:** DW01A + FS8205A in the pack's minus: over-charge 4.3 V, over-discharge 2.4 V,
  over-current about 3 A and short circuit, for the pack. Flat-top unprotected 18650 cells fit
  the holders.
- **Charger with power path:** a TI BQ24075 from the Pico's VBUS, in USB500 mode (at most 500 mA
  from the port), 800 mA fast charge (RISET 1.13 kΩ), input limit set by RILIM 1.18 kΩ, safety timers
  off (two cells in parallel charge longer than its longest timer; termination is by current), TS
  tied to 10 kΩ (no thermistor). Its output SYS runs the board from USB when one is plugged in and
  from the cells otherwise; SYS reaches the Pico's VSYS through a 1N5819HW Schottky, beside the
  Pico's own VBUS diode.
- **On/off:** the slide switch on the left edge pulls the Pico's 3V3_EN low (its buck-boost off; the
  charger still charges with the switch off).

| State | Current from the cells (estimate) |
|---|---|
| RP2040 at 270 MHz, both cores busy | ~50 mA at 3.3 V |
| SSD1309, half the pixels lit | ~15–25 mA |
| **Total** | **~70 mA at 3.3 V ≈ 0.25 W with losses → ~65 mA from 3.7 V** |

Two 3000 mAh cells → **about 90 h** of play (estimate). In USB500 mode the charger takes at most
500 mA from the port, the board's own draw included, so the cells charge at somewhat under 500 mA
(the 800 mA ISET setting is the ceiling, not reached): about 13 h for two empty cells, longer while
playing.

## Charging

Plug a USB charger or computer into the Pico's micro-USB. The red LED (CHG) is on while the cells
charge and goes out when they are full; the green LED (USB) is on while USB power is present. The
board runs from USB while it charges, switched on or off. Insert the cells with + at the end the
back's silkscreen marks.

## Modules plugged in by hand

The assembly solders two 1x20 female sockets and one 1x7 female socket; the modules are bought
separately and plugged in:

- **U1: Raspberry Pi Pico** (SC0915, with its male headers soldered on: the Pico H has them),
  on the back, components facing the board, the USB end at the top edge.
- **DS1: 2.42" 128 × 64 SSD1309 OLED module, SPI** (7 pins: GND, VCC, SCL, SDA, RES, DC, CS),
  on the front. Modules are sold set to I2C by default on some listings: buy the SPI version (or
  move its resistors as its seller describes).

## Storage

Everything is in the Pico's 2 MB flash: 1.8 MB of WHX and 260 KB of program, 31 KB to spare. Saving
games is left out for that (`NO_USE_SAVEGAME` in `doom/config.h`: the menu says so); the
registered/Ultimate WAD does not fit either: use a Pico with 16 MB (variant 04).

## Firmware: build and flash

- **Build:** in PCBKit, the Laboratory's **Build & run** builds `doom/` (Cortex-M0+, the kit's
  boot2 for the Pico's W25Q16 and its start-up); then export the firmware
  (`export.run { format: "firmware" }`): `U1.uf2`, the program and the WHX.
- **Flashing on arrival:** hold the Pico's BOOTSEL button and plug its micro-USB into a computer:
  it appears as the RPI-RP2 drive; copy `U1.uf2` onto it and the Pico restarts into the game. No
  programmer and nothing on the board to configure. (Or SWD with a Raspberry Pi Debug Probe on the
  Pico's three SWD pads.)

## Bill of materials

Rough cost at 10 pieces (estimates): Pico $4.00 · 2 × 20-pin sockets $0.60 · SSD1309 2.42" module
$9.00 · 8 buttons $2.30 · piezo $0.60 · switch $0.10 · charger, protection and passives $1.80 · two 18650 holders $9.80 · PCB $1.50 → **about $30** without the cells.

<!-- BOM -->
The assembly BOM as `pcbkit export --format fab` writes it (JLCPCB assembly: LCSC codes; the modules' lines are their sockets):

| Qty | Refs | Part | LCSC | Footprint |
|---|---|---|---|---|
| 2 | BT1, BT2 | 1042 | C5249310 | BatteryHolder_Keystone_1042_1x18650 |
| 1 | BZ1 | GPC12075YB-5V4000 | C252948 | Buzzer_D12.0mm_H7.5mm_P6.50mm |
| 1 | C1 | 100nF | C1525 | C_0402_1005Metric |
| 1 | D1 | 1N5819HW-7-F | C82544 | D_SOD-123 |
| 1 | DS1 | Female header 1x7 2.54 mm | C2932672 | OLED_2.42in_SPI_Socket_1x07_P2.54mm |
| 1 | Q1 | AO3401A | C15127 | SOT-23 |
| 1 | Q2 | FS8205A | C5148694 | TSSOP-8_4.4x2.93mm_P0.65mm |
| 1 | R1 | 100ohm | C17408 | R_0805_2012Metric |
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
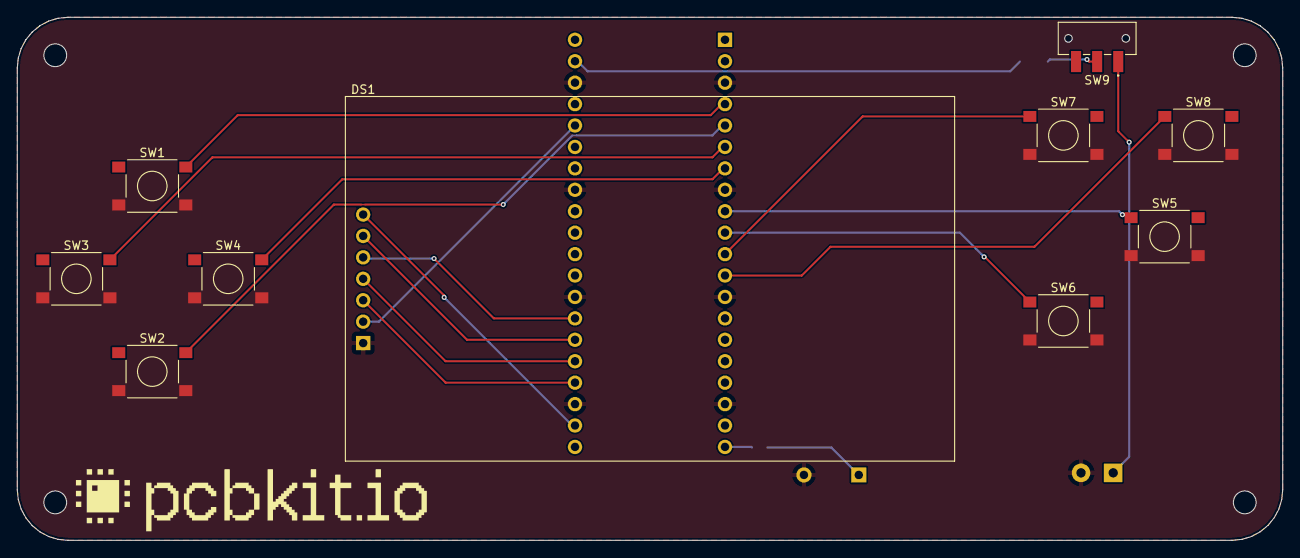
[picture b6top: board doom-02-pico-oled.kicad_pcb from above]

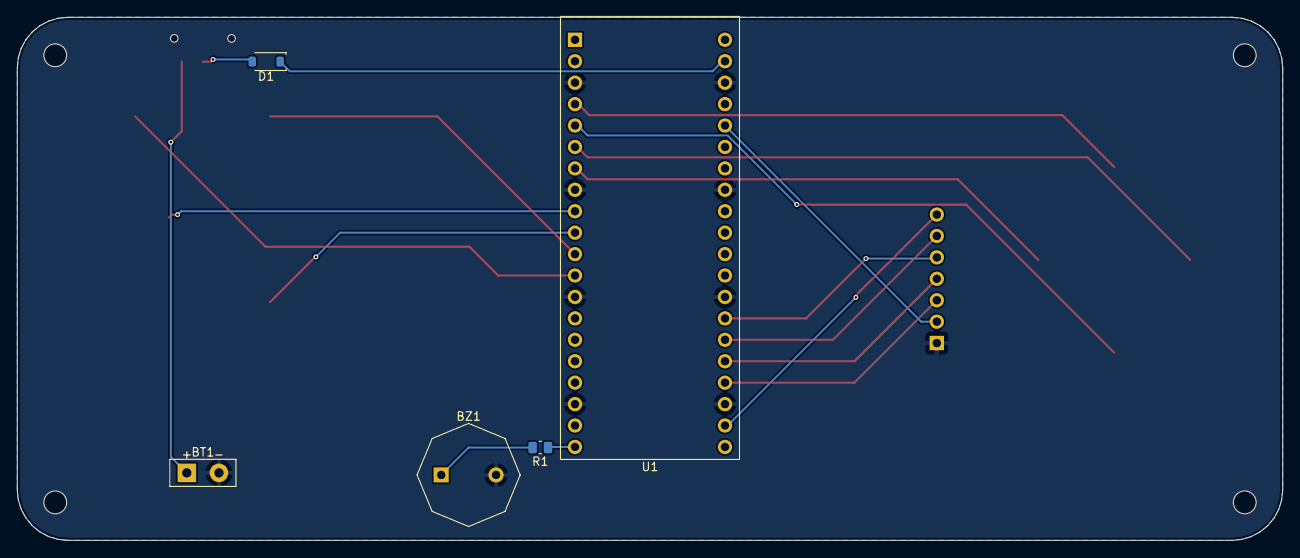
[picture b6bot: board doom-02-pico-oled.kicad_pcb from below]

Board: 2 copper layers, 150.0 x 62.0 mm, 20 parts (5 on the bottom side), 20 nets.

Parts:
BT1: 3xAA battery holder with leads; BatteryLeads_2x_D1.1mm_P3.81mm
BZ1: GPC12075YB-5V4000; Buzzer_D12.0mm_H7.5mm_P6.50mm
D1: schottky; D_SOD-123
DS1: MSP242X 2.42in 128x64 SPI module (SSD1309); OLED_2.42in_SPI_Socket_1x07_P2.54mm
H1, H2, H3, H4: MountingHole_2.7mm_M2.5
R1: 100ohm; R_0805_2012Metric
SW1, SW2, SW3, SW4, SW5, SW6, SW7, SW8: PTS645SM43SMTR92 LFS; SW_Tactile_SPST_6x6mm_SMD
SW9: JS102011SAQN; SW_Slide_SPDT_CK_JS102011SAQN_Horizontal
U1: SC0915; Raspberry_Pi_Pico_Socket_2x20_P2.54mm_W17.78mm
logo: Logo_PCBKit_pcbkit.io

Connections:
BUZZ: R1.1, U1.20
BUZZ_R: BZ1.1, R1.2
DOWN: SW2.1, SW2.2, U1.5
FIRE: SW5.1, SW5.2, U1.9
GND: BT1.2, BZ1.2, DS1.1, SW1.3, SW1.4, SW2.3, SW2.4, SW3.3, SW3.4, SW4.3, SW4.4, SW5.3, SW5.4, SW6.3, SW6.4, SW7.3, SW7.4, SW8.3, SW8.4, U1.3, U1.8, U1.13, U1.18, U1.23, U1.28, U1.33, U1.38
LEFT: SW3.1, SW3.2, U1.6
MENU: SW8.1, SW8.2, U1.12
MOSI: DS1.4, U1.25
OLED_CS: DS1.7, U1.22
OLED_DC: DS1.6, U1.26
OLED_RES: DS1.5, U1.27
RIGHT: SW4.1, SW4.2, U1.7
SCK: DS1.3, U1.24
STRAFE: SW7.1, SW7.2, U1.11
UP: SW1.1, SW1.2, U1.4
USE: SW6.1, SW6.2, U1.10
V3: DS1.2, U1.36
VBAT: BT1.1, SW9.1
VSW: D1.2, SW9.2
VSYS: D1.1, U1.39
